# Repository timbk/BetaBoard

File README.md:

# BetaBoard

A particle detector built for cost-effectiveness when ordered at O(100) pieces.

The detector concept is adapted from the [DIY Particle Detector Project](https://github.com/ozel/DIY_particle_detector) by Oliver Keller.

## Hardware Revisions

| Revision 1 | Revision 2 |
| :---: | :---: |
|  |  |
| [Schematic](hardware/betaBoard_r1.0/pdf/betaBoard_sch.pdf) [Layout](hardware/betaBoard_r1.0/pdf/betaBoard_pdf.pdf) | [Schematic](hardware/betaBoard_r2.0/betaBoard_r2.0_sch.pdf) [Layout](hardware/betaBoard_r2.0/betaBoard_r2.0_pcb.pdf) [Component Positions](hardware/betaBoard_r2.0/betaBoard_r2.0_positions.pdf) |
| Initial protoype: Working with adjustemtns to a few component values. Requires a lot of electrical and conductive tape to assemble. Designed for 16 diodes with the option to measure coincidences. | Streamlined redesign. Mainly adding a PCB casing to block light and radio imission. Attempting to add a simple alpha particle detector channel by stripping the isolation off of a diode (not successfull yet). Single channel with 6 diodes in parallel. Using additional ADC channels with less gain for debugging and potential experiments with scintillators. |

## Experiment Ideas

* Time distribution of pulses
* Rate vs distance (1/d^2 + offset)
* Absorption coefficient
    * Increase material thickness between detector and source
* Spectroscopy?? (alphas, sand down diode?
* Balloon in cellar

## Serial interface

* `T` `T <block_index> <timestamp_us> <overflow> # <sample_0> <sample_1> .. <sample_N>`
    * `block_index`: uint16_t, mainly relevant for debugging
    * `timestamp_us`: uint64_t, Trigger point timestamp in micro seconds since start of the measurement
    * `overflow`: bool, set to 1 if an overflow happend prior to this sample
    * `sample_n`:  int16_t, samples from the triggered waveform

## PCB

[Schematic](betaBoard/pdf/betaBoard_sch.pdf)
[Layout](betaBoard/pdf/betaBoard_pdf.pdf)

The goal was to keep it small to keep the PCB cost low and to make it fit easily.
Components were chosen to keep the price low and based on availablility at the chosen manufacturer.

## Ideas

* Strip detector with 4 pixels?
* File down SMD LEDs for less absorption?
* 3D-Printed Case?
* Interconnect multiple detectors?

## R2.0 ideas

* Put VCC on interconnect instead of 3V3
* Review diode cutout size
* Increase power supply castellated hole distance
* Increase LDO heat sink plane size
* Think about how usefull the coincidence concept is: 2x2 = 2+2 = 4!
* Silk to highlight Diode grouping
* Seperate bulk capacitor on 5V rail for analog

## Noise calculations

* Spice simulation: peak of ca. 40 $\mu\text{V}/\sqrt{\text{Hz}}$
    * Resistor thermal noise: $\sqrt{4k_BTR}\approx 400 ~ \text{nV/}\sqrt{\text{Hz}}$
    * LM358 input noise is ca. 40 $\text{nV}/\sqrt{\text{Hz}}$
    * Gain of second stage is ca. 100 for the peak frequency
    * => Resistor thermal noise is dominant part in simulation, LM385 noise should be negligible
        * $100 \cdot 400~\text{nV}/\sqrt{\text{Hz}} \approx 40~\mu\text{V}/\sqrt{\text{Hz}}$

## Potential signal sources

* 10g KCl has ca. 164 Bq.
* Estimate of geometric acceptency at 2 cm distance: $A = \frac{4 \cdot 7.5~\text{mm}^2} {4\pi\cdot (20~\text{mm})^2} \approx 0.006$
    * With perfect efficiency: ca. 1 Hz

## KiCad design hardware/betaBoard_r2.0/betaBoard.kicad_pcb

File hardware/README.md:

# Hardware Files

## betaBoard.pretty

Custom KiCad footprints.

## betaBoard_r1.0

First revision of the PCB.

Design concepts:
* 4 Channels
    * adding channles came without significant cost (only opamps and passives)
    * 2 Channel on the back are expensive to populate
* Header to connect PD with leads
* External power header for up to 12 V to increase diode bias
* RP2040 allows simple programming via USB
    * Can be done by the user without special tools
* Allow options for different diode placement
    * More diodes yield more sensitivity

Good:
* MCU, buttons, USB etc work perfectly out of the box :D

Challenges:
* High USB noise (1kHz spikes)
    * R14 requires a parallel C to get rid of noise from USB line
        * 1uF seems to help but does not seem sufficient (Could try 10uF, have 0603)
        * could increase R by factor 10
    * Try larger bulk capacitance (100uF or 1000uF)
        * 1000 uF seems to help!
        * Might be change in current draw
        * Cable length (resistance) seems to have an effect
    * Useing seperate diodes for the two supplies could help (diode voltage drop might depend on current)
    * TODO: Try if battery operation is better (helps to exclude potential points where 1 kHz noise couples)
* Is 40 MOhm working with the input impedance of LM358??
* Cut up groundplane at the PDs is probably not optimal
* Keep loop areas even smaller (I don't think it's the source of issues, but would feel better)
* USB port shielding is connected to GND. This might not be the optimal solution
    * Next: Add 2 0603 footprints? (allows open, short, 1MOhm+C)

## betaBoard_r1.1

Next revision. Work in progress.

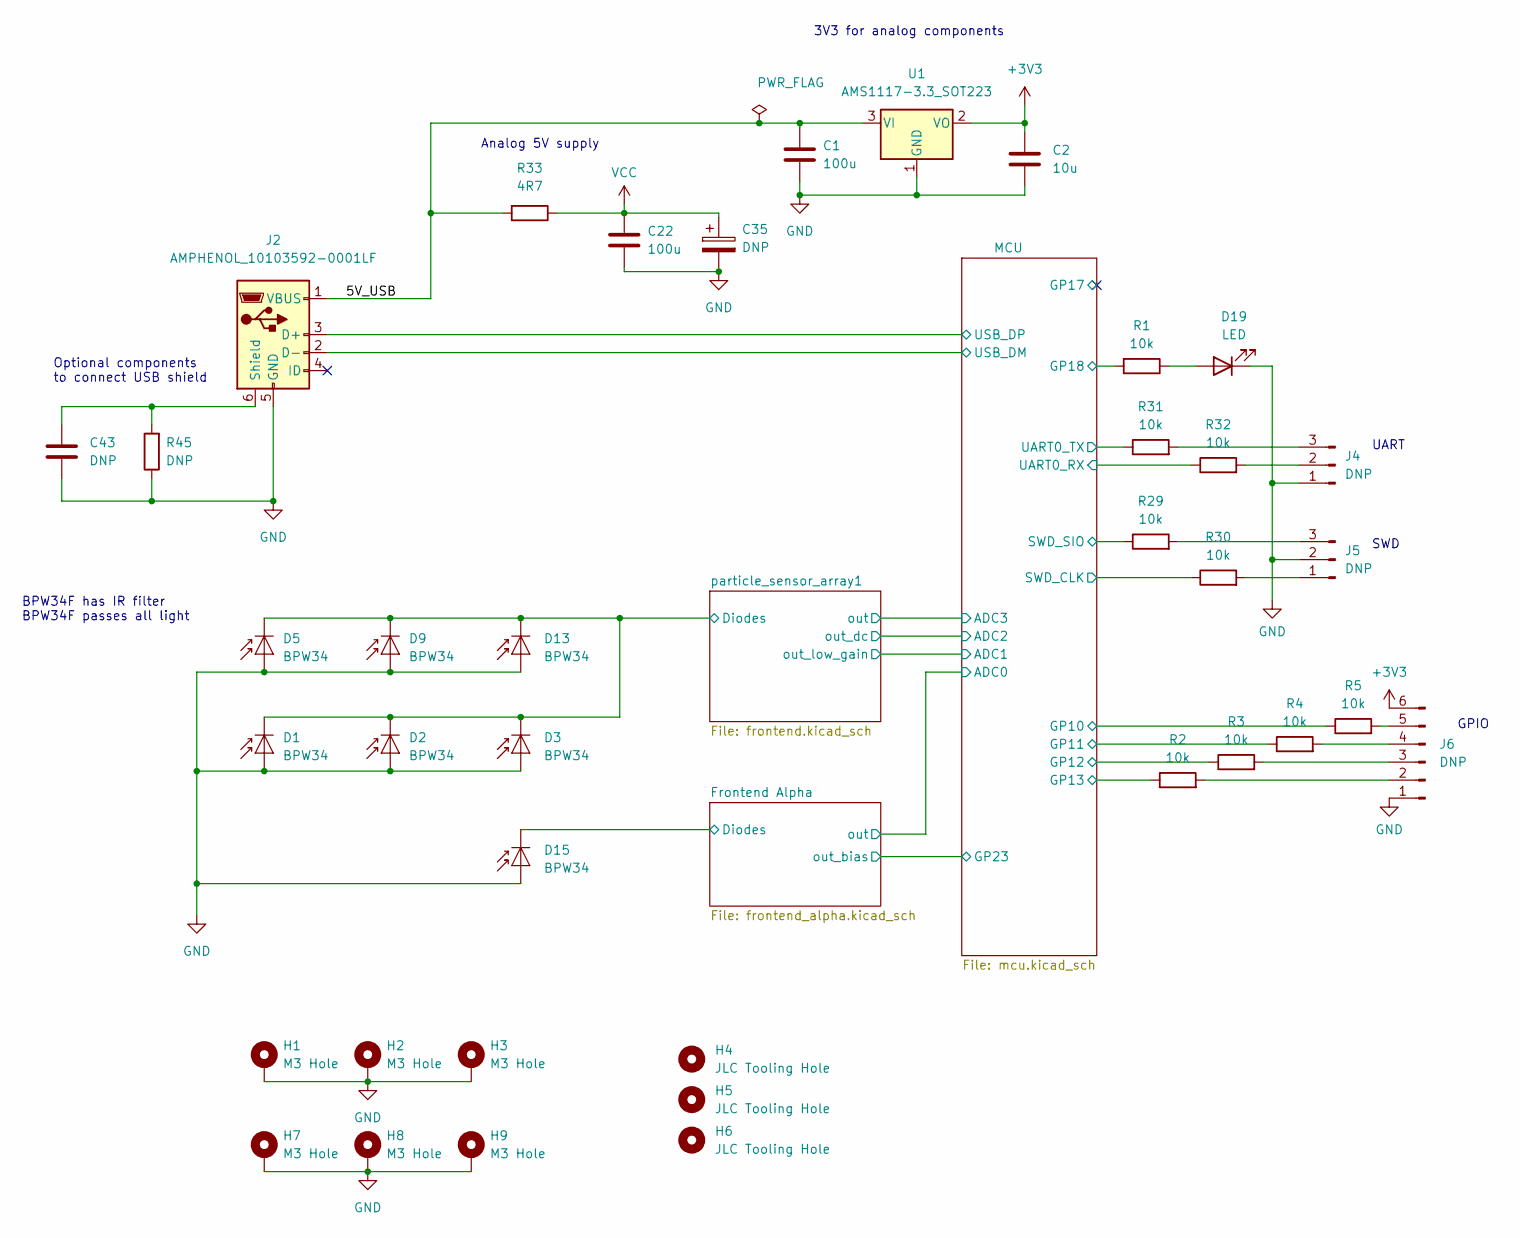
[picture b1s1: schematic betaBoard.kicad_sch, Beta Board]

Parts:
C1, C22: 100u; C_1206_3216Metric
C2: 10u; C_1206_3216Metric
C35: DNP; CP_Radial_D10.0mm_P5.00mm
C43: DNP; C_0603_1608Metric
D1, D2, D3, D5, D9, D13, D15: BPW34; Osram_BPW34S-SMD
D19: LED; LED_0603_1608Metric
H1, H2, H3, H7, H8, H9: M3 Hole; MountingHole_2.7mm_M2.5_DIN965_Pad
H4, H5, H6: JLC Tooling Hole; JLC_tooling_hole
J2: AMPHENOL_10103592-0001LF
J4, J5: DNP; PinHeader_1x03_P2.54mm_Vertical
J6: DNP; PinHeader_1x06_P2.54mm_Vertical
R1, R2, R3, R4, R5, R29, R30, R31, R32: 10k; R_0603_1608Metric
R33: 4R7; R_0603_1608Metric
R45: DNP; R_0603_1608Metric
U1: AMS1117-3.3_SOT223; SOT-223-3_TabPin2

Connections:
+3V3: C2.1, J6.6, U1.2 (VO); also elsewhere on the board
/5V_USB: C1.1, J2.1 (VBUS), R33.2, U1.3 (VI)
/Frontend Alpha/Diodes: D15.1 (K); also elsewhere on the board
/MCU/GP10: R5.1; also elsewhere on the board
/MCU/GP11: R4.1; also elsewhere on the board
/MCU/GP12: R3.1; also elsewhere on the board
/MCU/GP13: R2.1; also elsewhere on the board
/MCU/GP18: R1.2; also elsewhere on the board
/MCU/SWD_CLK: R30.1; also elsewhere on the board
/MCU/SWD_SIO: R29.1; also elsewhere on the board
/MCU/UART0_RX: R32.1; also elsewhere on the board
/MCU/UART0_TX: R31.1; also elsewhere on the board
/MCU/USB_DM: J2.2 (D-); also elsewhere on the board
/MCU/USB_DP: J2.3 (D+); also elsewhere on the board
/particle_sensor_array1/Diodes: D1.1 (K), D2.1 (K), D3.1 (K), D5.1 (K), D9.1 (K), D13.1 (K); also elsewhere on the board
GND: C1.2, C2.2, C22.2, C35.2, C43.2, D1.2 (A), D2.2 (A), D3.2 (A), D5.2 (A), D9.2 (A), D13.2 (A), D15.2 (A), D19.1 (K), H1.1, H2.1, H3.1, H7.1, H8.1, H9.1, J2.5 (GND), J4.1, J5.2, J6.1, R45.1, U1.1 (GND); also elsewhere on the board
unnamed: D19.2 (A), R1.1
unnamed: C43.1, J2.6 (Shield), R45.2
unnamed: J4.2, R32.2
unnamed: J4.3, R31.2
unnamed: J5.1, R30.2
unnamed: J5.3, R29.2
unnamed: J6.2, R2.2
unnamed: J6.3, R3.2
unnamed: J6.4, R4.2
unnamed: J6.5, R5.2
VCC: C22.1, C35.1, R33.1; also elsewhere on the board

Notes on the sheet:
SWD
GPIO
Analog 5V supply
3V3 for analog components
BPW34F has IR filter BPW34F passes all light
UART
Optional components to connect USB shield

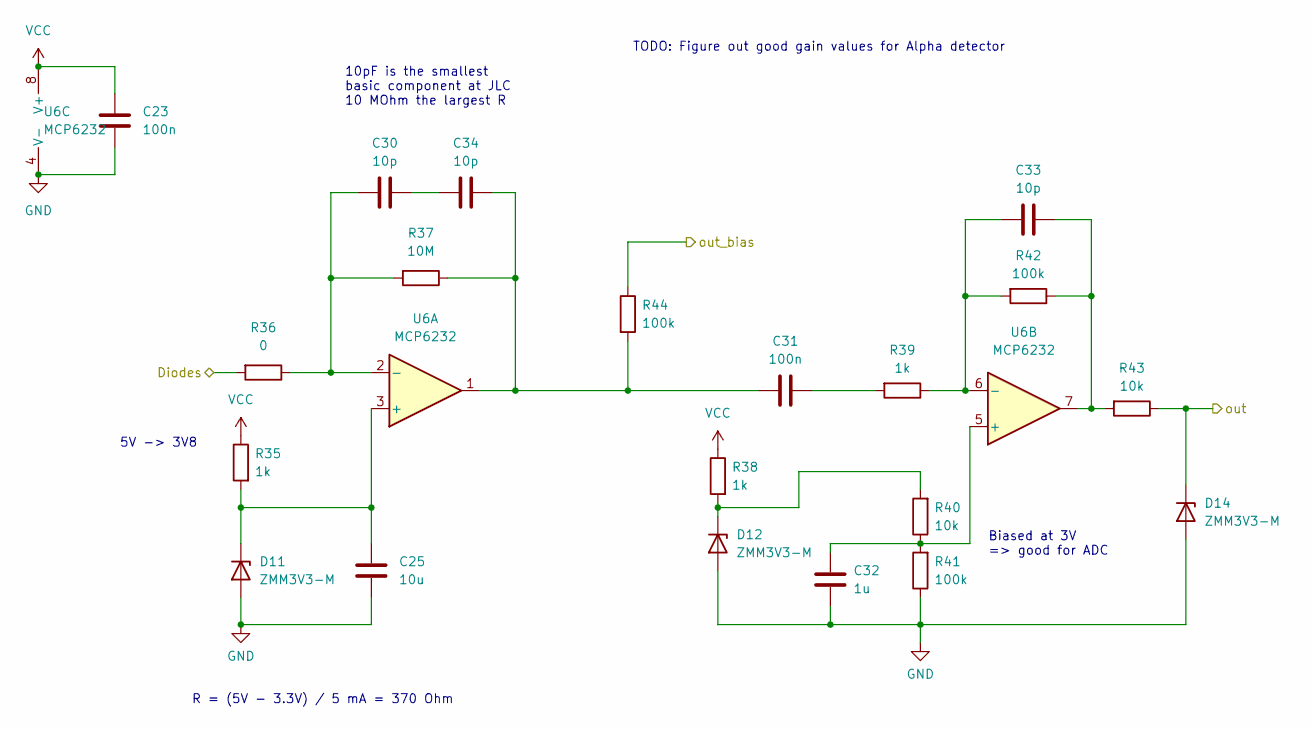
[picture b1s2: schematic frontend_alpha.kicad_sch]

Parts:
C23, C31: 100n; C_0603_1608Metric
C25: 10u; C_0603_1608Metric
C30, C33, C34: 10p; C_0603_1608Metric
C32: 1u; C_0603_1608Metric
D11, D12, D14: ZMM3V3-M; D_MiniMELF
R35, R38, R39: 1k; R_0603_1608Metric
R36: 0; R_0603_1608Metric
R37: 10M; R_0603_1608Metric
R40, R43: 10k; R_0603_1608Metric
R41, R42, R44: 100k; R_0603_1608Metric
U6: MCP6232; SOIC-8_3.9x4.9mm_P1.27mm

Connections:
/Frontend Alpha/Diodes: R36.2; also elsewhere on the board
/Frontend Alpha/out: D14.1 (K), R43.1; also elsewhere on the board
/Frontend Alpha/out_bias: R44.1; also elsewhere on the board
GND: C23.2, C25.2, C32.2, D11.2 (A), D12.2 (A), D14.2 (A), R41.1, U6.4 (V-); also elsewhere on the board
unnamed: C30.2, C34.1
unnamed: C31.1, C34.2, R37.1, R44.2, U6.1
unnamed: C31.2, R39.2
unnamed: C33.2, R42.1, R43.2, U6.7
unnamed: C25.1, D11.1 (K), R35.2, U6.3 (+)
unnamed: D12.1 (K), R38.2, R40.2
unnamed: C30.1, R36.1, R37.2, U6.2 (-)
unnamed: C32.1, R40.1, R41.2, U6.5 (+)
unnamed: C33.1, R39.1, R42.2, U6.6 (-)
VCC: C23.1, R35.1, R38.1, U6.8 (V+); also elsewhere on the board

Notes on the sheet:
5V -> 3V8
TODO: Figure out good gain values for Alpha detector
10pF is the smallest basic component at JLC 10 MOhm the largest R
R = (5V - 3.3V) / 5 mA = 370 Ohm
Biased at 3V => good for ADC

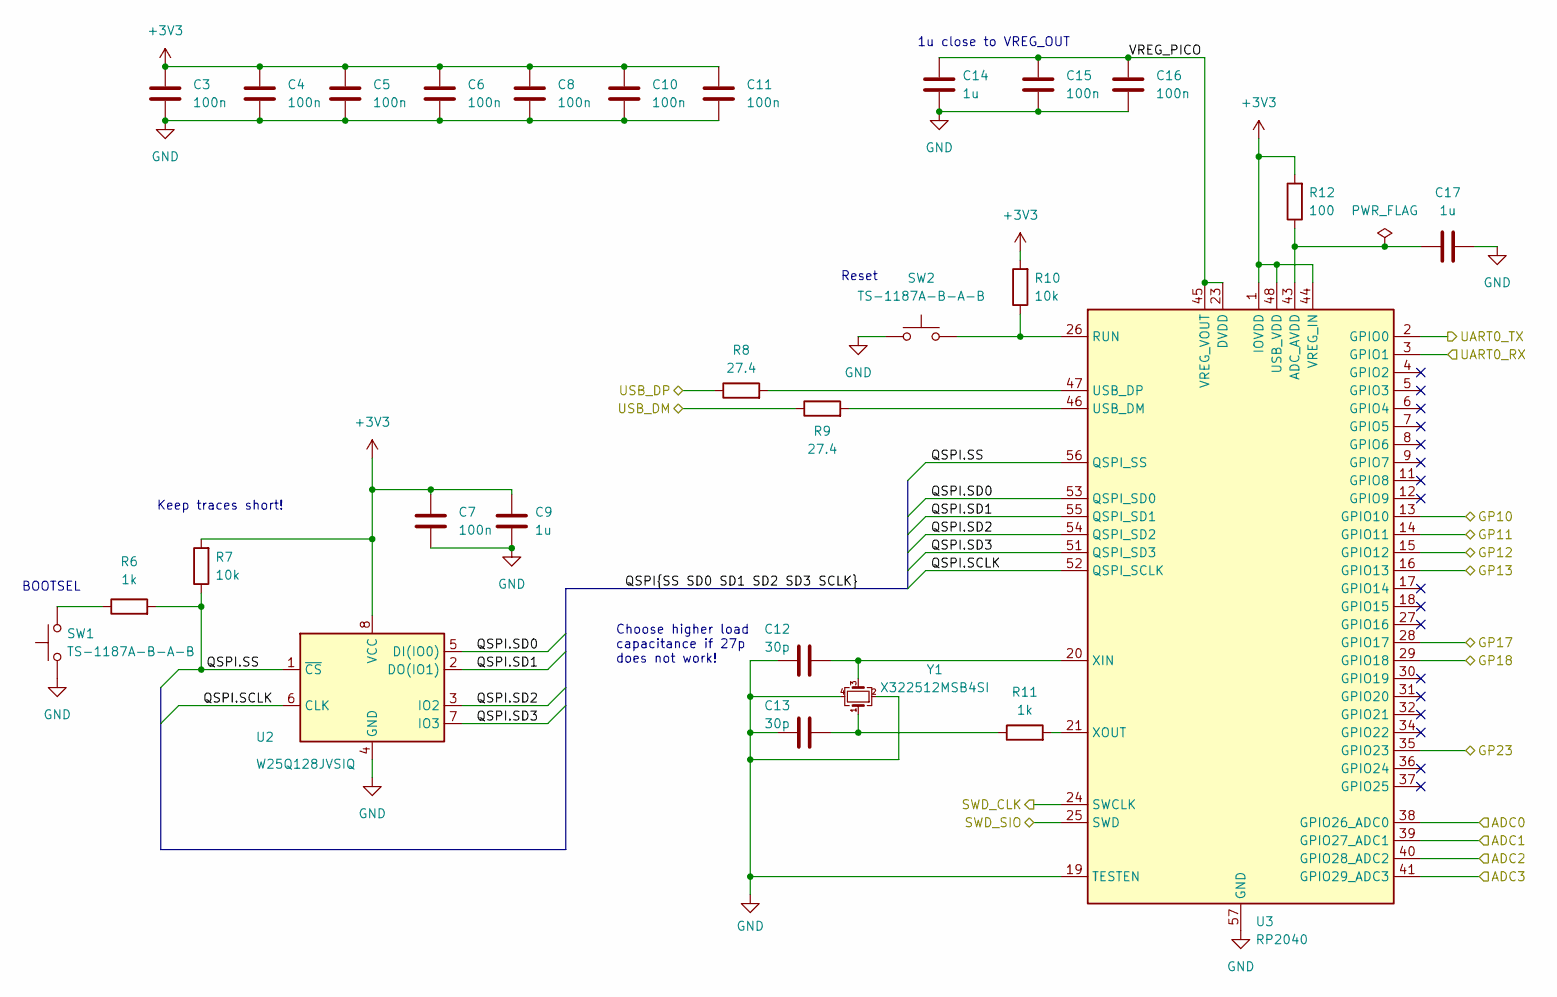
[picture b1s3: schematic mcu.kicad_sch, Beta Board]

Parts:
C3, C4, C5, C6, C7, C8, C10, C11, C15, C16: 100n; C_0603_1608Metric
C9, C14, C17: 1u; C_0603_1608Metric
C12, C13: 30p; C_0603_1608Metric
R6, R11: 1k; R_0603_1608Metric
R7, R10: 10k; R_0603_1608Metric
R8, R9: 27.4; R_0603_1608Metric
R12: 100; R_0603_1608Metric
SW1, SW2: TS-1187A-B-A-B
U2: W25Q128JVSIQ; SOIC-8_5.23x5.23mm_P1.27mm
U3: RP2040; QFN-56-1EP_7x7mm_P0.4mm_EP3.2x3.2mm
Y1: X322512MSB4SI; Crystal_SMD_3225-4Pin_3.2x2.5mm

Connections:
+3V3: C3.1, C4.1, C5.1, C6.1, C7.1, C8.1, C9.1, C10.1, C11.1, R7.2, R10.2, R12.2, U2.8 (VCC), U3.1 (IOVDD), U3.10 (IOVDD), U3.22 (IOVDD), U3.33 (IOVDD), U3.42 (IOVDD), U3.44 (VREG_IN), U3.48 (USB_VDD), U3.49 (IOVDD); also elsewhere on the board
/Frontend Alpha/out: U3.38 (GPIO26_ADC0); also elsewhere on the board
/Frontend Alpha/out_bias: U3.35 (GPIO23); also elsewhere on the board
/MCU/ADC1: U3.39 (GPIO27_ADC1); also elsewhere on the board
/MCU/ADC2: U3.40 (GPIO28_ADC2); also elsewhere on the board
/MCU/ADC3: U3.41 (GPIO29_ADC3); also elsewhere on the board
/MCU/GP10: U3.13 (GPIO10); also elsewhere on the board
/MCU/GP11: U3.14 (GPIO11); also elsewhere on the board
/MCU/GP12: U3.15 (GPIO12); also elsewhere on the board
/MCU/GP13: U3.16 (GPIO13); also elsewhere on the board
/MCU/GP17: U3.28 (GPIO17)
/MCU/GP18: U3.29 (GPIO18); also elsewhere on the board
/MCU/QSPI.SCLK: U2.6 (CLK), U3.52 (QSPI_SCLK)
/MCU/QSPI.SD0: U2.5 (DI(IO0)), U3.53 (QSPI_SD0)
/MCU/QSPI.SD1: U2.2 (DO(IO1)), U3.55 (QSPI_SD1)
/MCU/QSPI.SD2: U2.3 (IO2), U3.54 (QSPI_SD2)
/MCU/QSPI.SD3: U2.7 (IO3), U3.51 (QSPI_SD3)
/MCU/QSPI.SS: R6.2, R7.1, U2.1 (~CS), U3.56 (QSPI_SS)
/MCU/SWD_CLK: U3.24 (SWCLK); also elsewhere on the board
/MCU/SWD_SIO: U3.25 (SWD); also elsewhere on the board
/MCU/UART0_RX: U3.3 (GPIO1); also elsewhere on the board
/MCU/UART0_TX: U3.2 (GPIO0); also elsewhere on the board
/MCU/USB_DM: R9.1; also elsewhere on the board
/MCU/USB_DP: R8.1; also elsewhere on the board
/MCU/VREG_PICO: C14.1, C15.1, C16.1, U3.23 (DVDD), U3.45 (VREG_VOUT), U3.50 (DVDD)
GND: C3.2, C4.2, C5.2, C6.2, C7.2, C8.2, C9.2, C10.2, C11.2, C12.1, C13.2, C14.2, C15.2, C16.2, C17.2, SW1.1, SW2.1, U2.4 (GND), U3.19 (TESTEN), U3.57 (GND), Y1.2, Y1.4; also elsewhere on the board
unnamed: C13.1, R11.1, Y1.1
unnamed: R6.1, SW1.2
unnamed: C17.1, R12.1, U3.43 (ADC_AVDD)
unnamed: R10.1, SW2.2, U3.26 (RUN)
unnamed: R9.2, U3.46 (USB_DM)
unnamed: R8.2, U3.47 (USB_DP)
unnamed: C12.2, U3.20 (XIN), Y1.3
unnamed: R11.2, U3.21 (XOUT)

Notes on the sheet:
Choose higher load capacitance if 27p does not work!
Reset
Keep traces short!
1u close to VREG_OUT
BOOTSEL

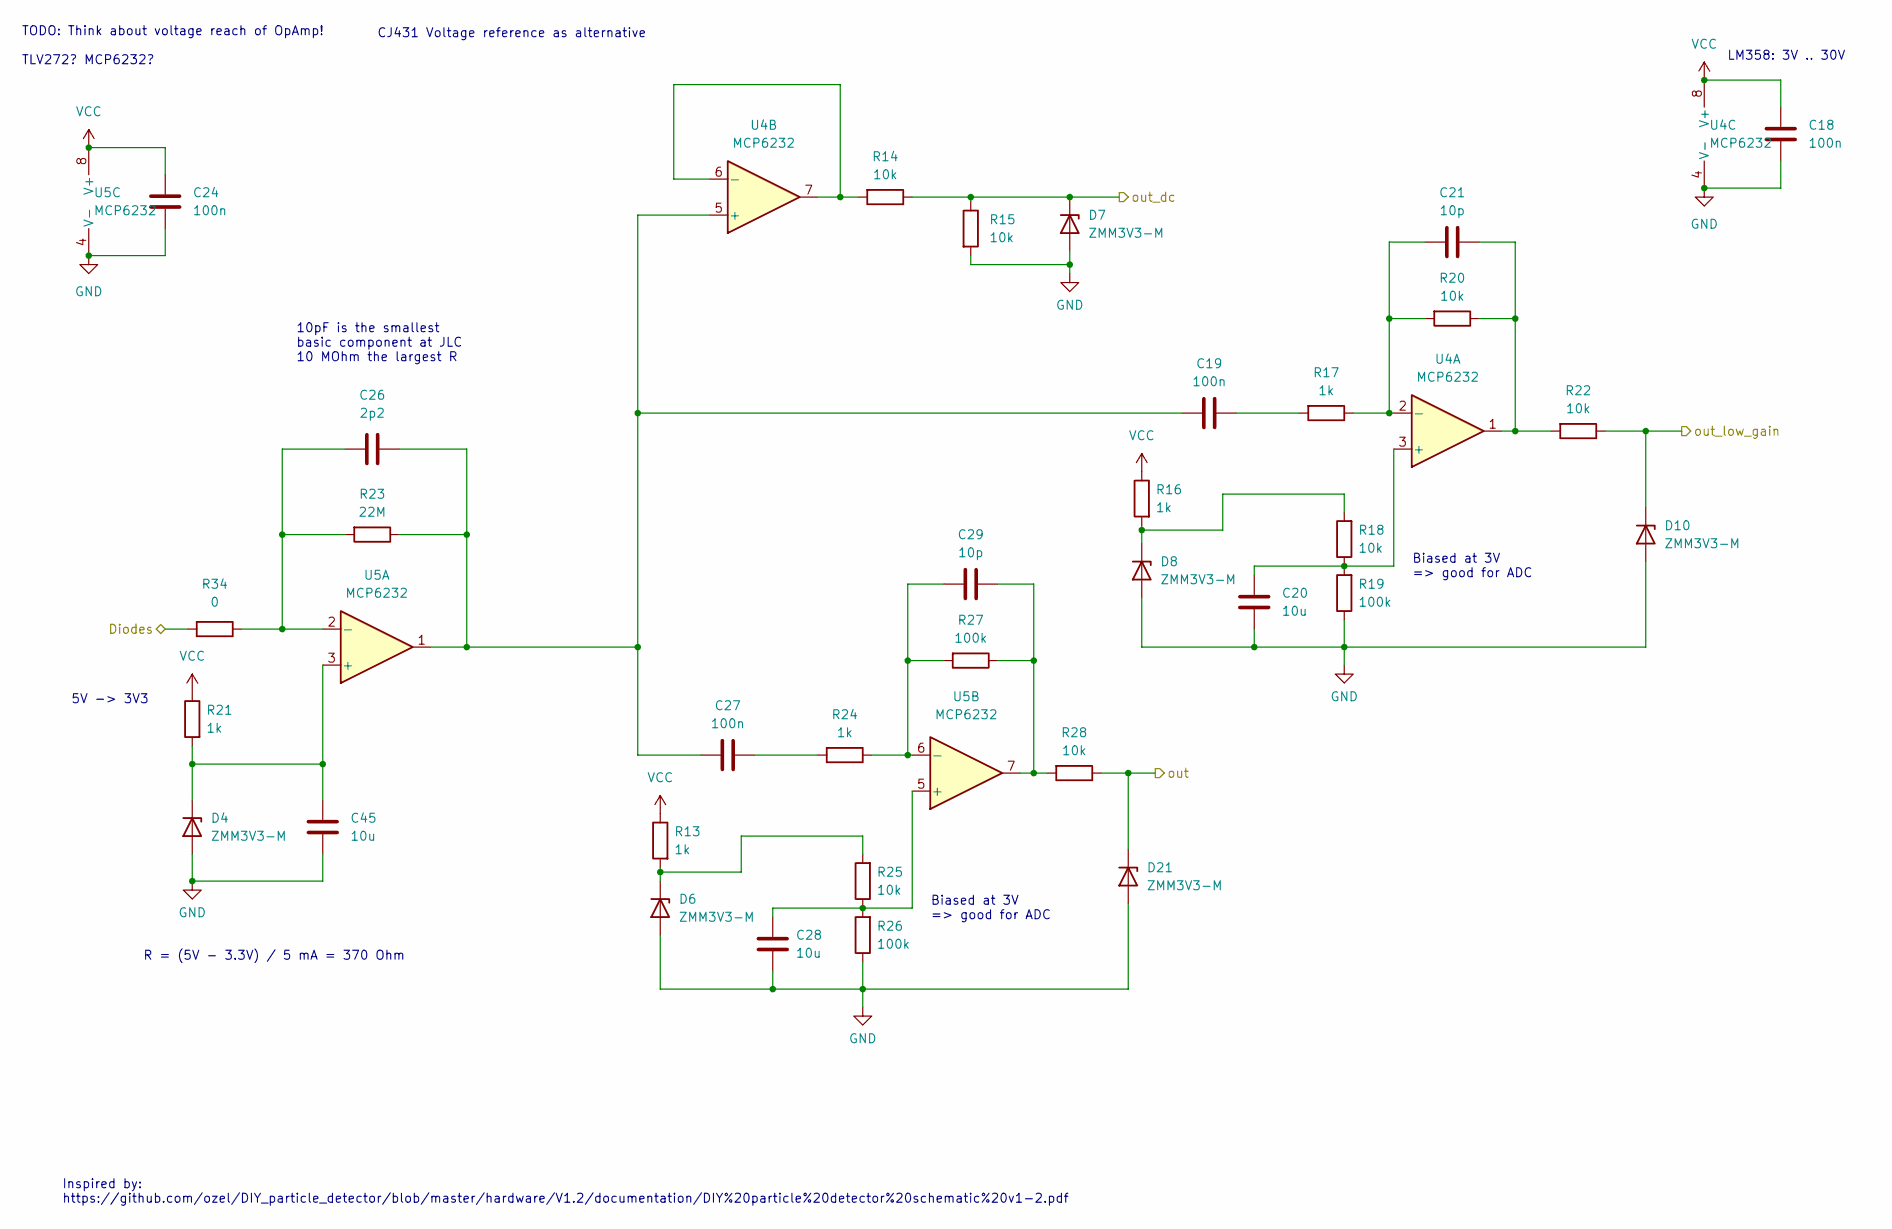
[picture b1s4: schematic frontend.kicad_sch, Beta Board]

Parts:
C18, C19, C24, C27: 100n; C_0603_1608Metric
C20, C28, C45: 10u; C_0603_1608Metric
C21, C29: 10p; C_0603_1608Metric
C26: 2p2; C_0603_1608Metric
D4, D6, D7, D8, D10, D21: ZMM3V3-M; D_MiniMELF
R13, R16, R17, R21, R24: 1k; R_0603_1608Metric
R14, R15, R18, R20, R22, R25, R28: 10k; R_0603_1608Metric
R19, R26, R27: 100k; R_0603_1608Metric
R23: 22M; R_0603_1608Metric
R34: 0; R_0603_1608Metric
U4, U5: MCP6232; SOIC-8_3.9x4.9mm_P1.27mm

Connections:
/MCU/ADC1: D10.1 (K), R22.1; also elsewhere on the board
/MCU/ADC2: D7.1 (K), R14.1, R15.1; also elsewhere on the board
/MCU/ADC3: D21.1 (K), R28.1; also elsewhere on the board
/particle_sensor_array1/Diodes: R34.2; also elsewhere on the board
GND: C18.2, C20.2, C24.2, C28.2, C45.2, D4.2 (A), D6.2 (A), D7.2 (A), D8.2 (A), D10.2 (A), D21.2 (A), R15.2, R19.1, R26.1, U4.4 (V-), U5.4 (V-); also elsewhere on the board
unnamed: C19.2, R17.2
unnamed: C21.2, R20.1, R22.2, U4.1
unnamed: C27.2, R24.2
unnamed: C29.2, R27.1, R28.2, U5.7
unnamed: C45.1, D4.1 (K), R21.2, U5.3 (+)
unnamed: D6.1 (K), R13.2, R25.2
unnamed: D8.1 (K), R16.2, R18.2
unnamed: C20.1, R18.1, R19.2, U4.3 (+)
unnamed: C21.1, R17.1, R20.2, U4.2 (-)
unnamed: C19.1, C26.2, C27.1, R23.1, U4.5 (+), U5.1
unnamed: R14.2, U4.6 (-), U4.7
unnamed: C26.1, R23.2, R34.1, U5.2 (-)
unnamed: C28.1, R25.1, R26.2, U5.5 (+)
unnamed: C29.1, R24.1, R27.2, U5.6 (-)
VCC: C18.1, C24.1, R13.1, R16.1, R21.1, U4.8 (V+), U5.8 (V+); also elsewhere on the board

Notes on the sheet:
Inspired by: https://github.com/ozel/DIY_particle_detector/blob/master/hardware/V1.2/documentation/DIY%20particle%20detector%20schematic%20v1-2.pdf
TODO: Think about voltage reach of OpAmp! TLV272? MCP6232?
5V -> 3V3
CJ431 Voltage reference as alternative
10pF is the smallest basic component at JLC 10 MOhm the largest R
Biased at 3V => good for ADC
R = (5V - 3.3V) / 5 mA = 370 Ohm
LM358: 3V .. 30V

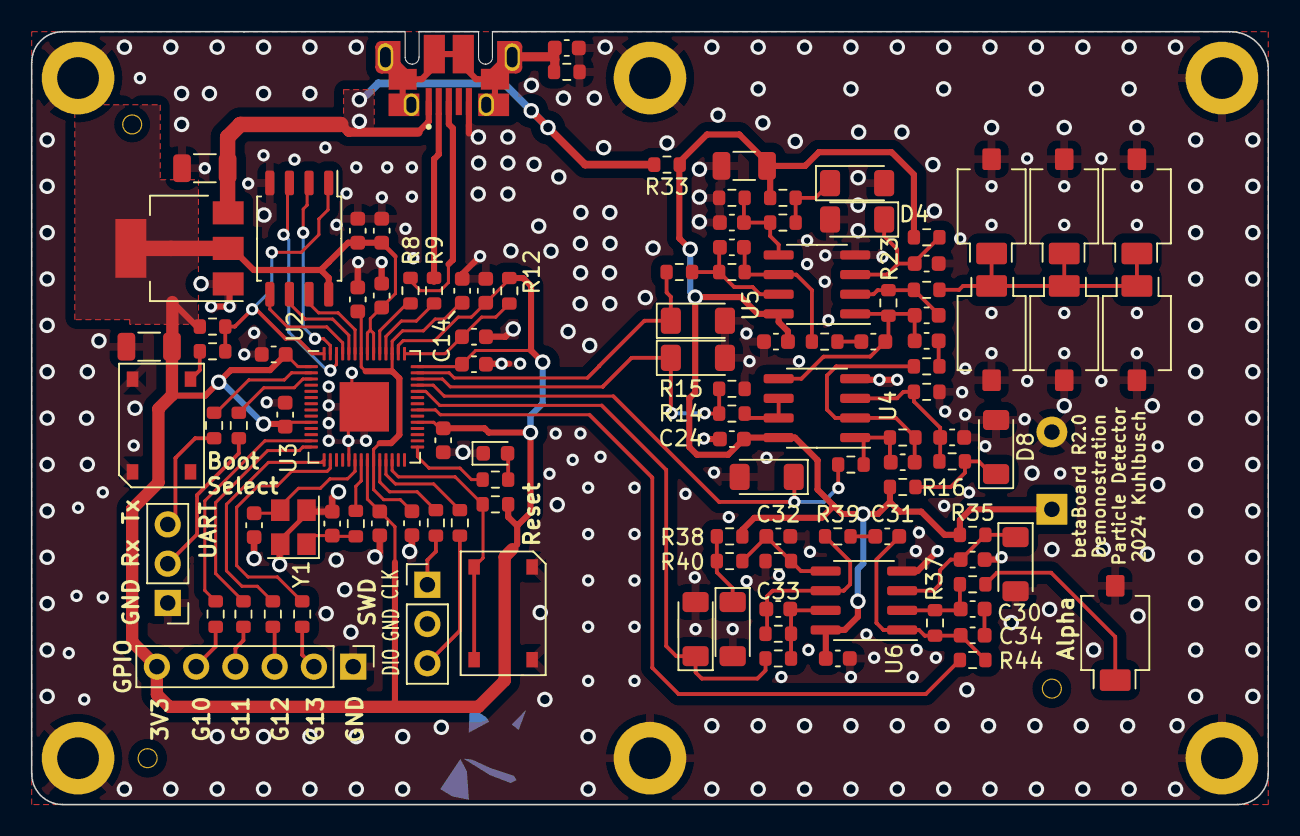
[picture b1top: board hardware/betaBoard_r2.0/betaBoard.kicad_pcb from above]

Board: 2 copper layers, 80.0 x 50.0 mm, 121 parts (1 on the bottom side), 70 nets.

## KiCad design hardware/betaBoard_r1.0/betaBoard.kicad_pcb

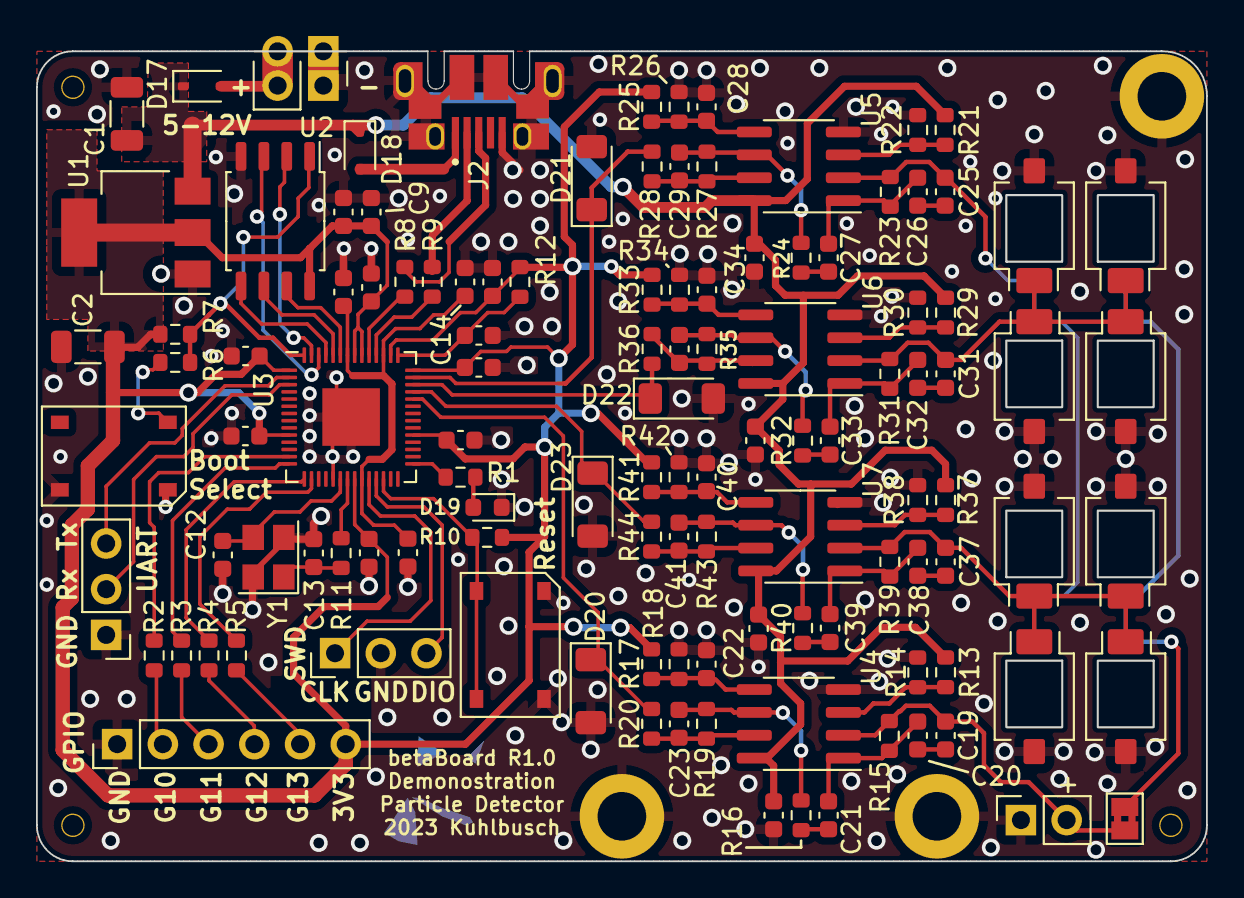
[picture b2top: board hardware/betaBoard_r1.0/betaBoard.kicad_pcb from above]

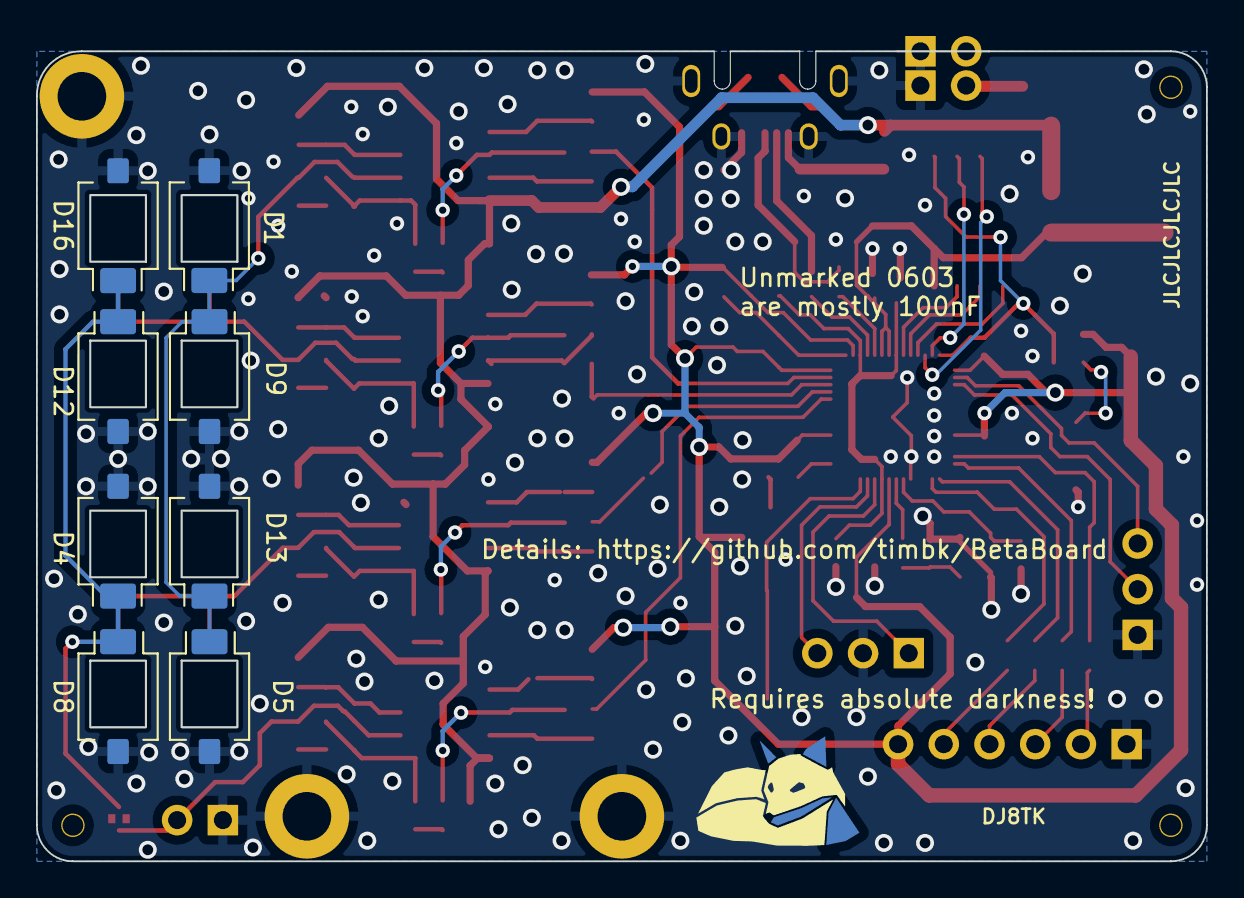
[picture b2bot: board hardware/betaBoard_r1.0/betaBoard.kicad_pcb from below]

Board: 2 copper layers, 65.0 x 45.0 mm, 131 parts (8 on the bottom side), 73 nets.

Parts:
C1, C2: 10u; C_1206_3216Metric
C3, C4, C5, C6, C7, C8, C10, C11, C15, C16, C18, C22, C24, C28, C30, C34, C36, C40: 100n; C_0603_1608Metric
C9, C14, C17: 1u; C_0603_1608Metric
C12, C13: 30p; C_0603_1608Metric
C19, C20, C25, C26, C31, C32, C37, C38: 10p; C_0603_1608Metric
C21, C27, C33, C39: 470n; C_0603_1608Metric
C23, C29, C35, C41: 47p; C_0603_1608Metric
D1, D4, D5, D8, D9, D12, D13, D16: DNP; Osram_BPW34S-SMD
D2, D3, D6, D7, D10, D11, D14, D15: BPW34-SMD; Osram_BPW34S-SMD_hole
D17, D18: 1N5819WS; D_SOD-323
D19: LED; LED_0603_1608Metric
D20, D21, D22, D23: ZMM3V3-M; D_MiniMELF
H1, H2, H3: M3 Hole; MountingHole_2.7mm_M2.5_DIN965_Pad
H4, H5, H6: JLC Tooling Hole; JLC_tooling_hole
J1: DNP; PinHeader_1x02_P2.54mm_castellation
J2: AMPHENOL_10103592-0001LF
J3: DNP; PinSocket_1x02_P2.54mm_Vertical
J4, J5: DNP; PinHeader_1x03_P2.54mm_Vertical
J6: DNP; PinHeader_1x06_P2.54mm_Vertical
JP1: DNP; SolderJumper-2_P1.3mm_Bridged2Bar_Pad1.0x1.5mm
R1, R7, R10, R17, R18, R20, R25, R26, R28, R33, R34, R36, R41, R42, R44: 10k; R_0603_1608Metric
R2, R3, R4, R5, R6, R11: 1k; R_0603_1608Metric
R8, R9: 27.4; R_0603_1608Metric
R12: 100; R_0603_1608Metric
R13, R21, R29, R37: 4k7; R_0603_1608Metric
R14, R22, R30, R38: 15k; R_0603_1608Metric
R15, R23, R31, R39: 47M; R_0603_1608Metric
R16, R24, R32, R40: 4K7; R_0603_1608Metric
R19, R27, R35, R43: 1M; R_0603_1608Metric
SW1, SW2: C26638; TS-1187A-B-A-B
U1: AMS1117-3.3_SOT223; SOT-223-3_TabPin2
U2: W25Q128JVSIQ; SOIC-8_5.23x5.23mm_P1.27mm
U3: RP2040; QFN-56-1EP_7x7mm_P0.4mm_EP3.2x3.2mm
U4, U5, U6, U7: LM358; SOIC-8_3.9x4.9mm_P1.27mm
Y1: X322512MSB4SI; Crystal_SMD_3225-4Pin_3.2x2.5mm

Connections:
+3V3: C2.1, C3.1, C4.1, C5.1, C6.1, C7.1, C8.1, C9.1, C10.1, C11.1, J6.6, R7.2, R10.2, R12.2, R17.2, R25.2, R33.2, R41.2, U1.2 (VO), U2.8 (VCC), U3.1 (IOVDD), U3.10 (IOVDD), U3.22 (IOVDD), U3.33 (IOVDD), U3.42 (IOVDD), U3.44 (VREG_IN), U3.48 (USB_VDD), U3.49 (IOVDD)
/5V_USB: D18.2 (A), J2.1 (VBUS)
/MCU/ADC0: D20.1 (K), R20.1, U3.38 (GPIO26_ADC0)
/MCU/ADC1: D23.1 (K), R44.1, U3.39 (GPIO27_ADC1)
/MCU/ADC2: D22.1 (K), R36.1, U3.40 (GPIO28_ADC2)
/MCU/ADC3: D21.1 (K), R28.1, U3.41 (GPIO29_ADC3)
/MCU/GP10: R2.1, U3.13 (GPIO10)
/MCU/GP11: R3.1, U3.14 (GPIO11)
/MCU/GP12: R4.1, U3.15 (GPIO12)
/MCU/GP13: R5.1, U3.16 (GPIO13)
/MCU/GP18: R1.2, U3.29 (GPIO18)
/MCU/QSPI.SCLK: U2.6 (CLK), U3.52 (QSPI_SCLK)
/MCU/QSPI.SD0: U2.5 (DI(IO0)), U3.53 (QSPI_SD0)
/MCU/QSPI.SD1: U2.2 (DO(IO1)), U3.55 (QSPI_SD1)
/MCU/QSPI.SD2: U2.3 (IO2), U3.54 (QSPI_SD2)
/MCU/QSPI.SD3: U2.7 (IO3), U3.51 (QSPI_SD3)
/MCU/QSPI.SS: R6.2, R7.1, U2.1 (~CS), U3.56 (QSPI_SS)
/MCU/SWD_CLK: J5.1, U3.24 (SWCLK)
/MCU/SWD_SIO: J5.3, U3.25 (SWD)
/MCU/UART0_RX: J4.2, U3.3 (GPIO1)
/MCU/UART0_TX: J4.3, U3.2 (GPIO0)
/MCU/USB_DM: J2.2 (D-), R9.1
/MCU/USB_DP: J2.3 (D+), R8.1
/MCU/VREG_PICO: C14.1, C15.1, C16.1, U3.23 (DVDD), U3.45 (VREG_VOUT), U3.50 (DVDD)
/particle_sensor_array1/Diodes: C25.1, D1.1 (K), D5.1 (K), D9.1 (K), D13.1 (K), R23.2, U5.2 (-)
/particle_sensor_array2/Diodes: C31.1, D2.1 (K), D6.1 (K), D10.1 (K), D14.1 (K), R31.2, U6.2 (-)
/particle_sensor_array3/Diodes: C37.1, D3.1 (K), D7.1 (K), D11.1 (K), D15.1 (K), R39.2, U7.2 (-)
/particle_sensor_array/Diodes: C19.1, J3.2, JP1.2 (B), R15.2, U4.2 (-)
GND: C1.2, C2.2, C3.2, C4.2, C5.2, C6.2, C7.2, C8.2, C9.2, C10.2, C11.2, C12.1, C13.2, C14.2, C15.2, C16.2, C17.2, C18.2, C22.2, C24.2, C28.2, C30.2, C34.2, C36.2, C40.2, D1.2 (A), D2.2 (A), D3.2 (A), D4.2 (A), D5.2 (A), D6.2 (A), D7.2 (A), D8.2 (A), D9.2 (A), D10.2 (A), D11.2 (A), D12.2 (A), D13.2 (A), D14.2 (A), D15.2 (A), D16.2 (A), D19.1 (K), D20.2 (A), D21.2 (A), D22.2 (A), D23.2 (A), H1.1, H2.1, H3.1, J1.1, J2.5 (GND), J2.6 (Shield), J3.1, J4.1, J5.2, J6.1, R14.2, R18.1, R22.2, R26.1, R30.2, R34.1, R38.2, R42.1, SW1.1, SW2.1, U1.1 (GND), U2.4 (GND), U3.19 (TESTEN), U3.57 (GND), U4.4 (V-), U5.4 (V-), U6.4 (V-), U7.4 (V-), Y1.2, Y1.4
unnamed: C13.1, R11.1, Y1.1
unnamed: C19.2, C20.1
unnamed: C20.2, C21.1, R15.1, U4.1
unnamed: C21.2, R16.2
unnamed: C23.2, R19.1, R20.2, U4.7
unnamed: C25.2, C26.1
unnamed: C26.2, C27.1, R23.1, U5.1
unnamed: C27.2, R24.2
unnamed: C29.2, R27.1, R28.2, U5.7
unnamed: C31.2, C32.1
unnamed: C32.2, C33.1, R31.1, U6.1
unnamed: C33.2, R32.2
unnamed: C35.2, R35.1, R36.2, U6.7
unnamed: C37.2, C38.1
unnamed: C38.2, C39.1, R39.1, U7.1
unnamed: C39.2, R40.2
unnamed: C41.2, R43.1, R44.2, U7.7
unnamed: D4.1 (K), D8.1 (K), D12.1 (K), D16.1 (K), JP1.1 (A)
unnamed: D17.2 (A), J1.2
unnamed: D19.2 (A), R1.1
unnamed: J6.2, R2.2
unnamed: J6.3, R3.2
unnamed: J6.4, R4.2
unnamed: J6.5, R5.2
unnamed: R6.1, SW1.2
unnamed: C17.1, R12.1, U3.43 (ADC_AVDD)
unnamed: R10.1, SW2.2, U3.26 (RUN)
unnamed: R9.2, U3.46 (USB_DM)
unnamed: R8.2, U3.47 (USB_DP)
unnamed: C12.2, U3.20 (XIN), Y1.3
unnamed: R11.2, U3.21 (XOUT)
unnamed: R13.2, R14.1, U4.3 (+)
unnamed: C22.1, R17.1, R18.2, U4.5 (+)
unnamed: C23.1, R16.1, R19.2, U4.6 (-)
unnamed: R21.2, R22.1, U5.3 (+)
unnamed: C28.1, R25.1, R26.2, U5.5 (+)
unnamed: C29.1, R24.1, R27.2, U5.6 (-)
unnamed: R29.2, R30.1, U6.3 (+)
unnamed: C34.1, R33.1, R34.2, U6.5 (+)
unnamed: C35.1, R32.1, R35.2, U6.6 (-)
unnamed: R37.2, R38.1, U7.3 (+)
unnamed: C40.1, R41.1, R42.2, U7.5 (+)
unnamed: C41.1, R40.1, R43.2, U7.6 (-)
VCC: C1.1, C18.1, C24.1, C30.1, C36.1, D17.1 (K), D18.1 (K), R13.1, R21.1, R29.1, R37.1, U1.3 (VI), U4.8 (V+), U5.8 (V+), U6.8 (V+), U7.8 (V+)

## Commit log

2023-12-28 add custom footprints
2023-12-28 add r1.0 design files
2023-12-28 add schematic and PCB overview PDF
2023-12-28 add readme and images
2023-12-28 add PDFs and production file update (no significant changes)
2023-12-28 add license statement
2024-01-09 final ordered R1.0 pcb
2024-01-09 update gitignore
2024-01-18 commit old notes in README
2024-01-18 start micropython readout
2024-01-18 add notes on R1 commissioning to README
2024-01-18 add image of R1.0 PCB
2024-01-21 start c++ firmware (starting with ADC DMA stuff)
2024-01-21 add more notes on r1.0 to README
2024-01-21 adjustments in trying to get digitization to work properly
2024-01-21 add version info during compilation
2024-01-21 create other folder to clean up the main folder
2024-01-22 first pulse recordings
2024-01-24 clean up main.cpp
2024-01-24 adjust the adc data queue to add timestamps and block indices
2024-01-24 add timestamps and overflow status to trigger waveform print
2024-01-24 implement basic user interface
2024-01-24 implement more user interface commands
2024-01-27 start implementing a python interface
2024-01-27 clean up serial interface implementation
2024-01-27 move all hardware files to one folder
2024-01-27 more moving of folders
2024-01-27 add a readme to old micropython firmware folder
2024-01-27 notes on noise levels
2024-01-27 add basic spice simulations
2024-01-27 add noise analysis script
2024-01-27 add noise measuremnt result and KCl rate
2024-01-27 fix README
2024-01-28 implement a way to record triggered waveforms with python interface
2024-01-28 commit old python interface script status before cleaning up
2024-01-28 move python interface to top level folder
2024-01-28 move source code to a seperate folder to clean up the firmware build environment
2024-01-28 add info on building and flashing
2024-01-28 adjustment to README
2024-01-28 adjust READMEs
2024-01-28 add action that builds the firmware
2024-01-28 remove unused usb library import that adds a dependency
2024-01-28 add build status badge to README
2024-01-28 Add Actions (#1)
    * add action that builds the firmware
    * remove unused usb library import that adds a dependency
    * add build status badge to README
2024-01-28 python interface: add live plotting to main and read sample rate from device
2024-01-28 firmware: implement more effecient HPF
2024-01-28 add script to record measurements
2024-01-28 implement full waveform triggers on sample block edges
2024-01-28 adjustments to python readout for new variables
2024-01-28 fix off-by one affecting waveform length in edge cases
2024-02-04 start with r2.0
2024-02-07 main r2.0 design done
2024-02-07 add r2.0 mid panel pcb
2024-02-07 add top panel pcb
2024-03-13 adjust HPF design to be closer to limit
2024-03-13 add command to switch adc channel
2024-03-13 add command to disable blinking led
2024-03-13 add command to retrieve unique flash id
2024-03-13 clean up plotting and improve buffer clearing in python scripts
2024-07-02 add r2.0 schematic
2024-07-14 Update README.md
    Fixing links and starting to represent revision 2 correctly in the readme.
2024-07-14 add picture for README
2024-07-14 Update README.md
    Center table content
2024-07-14 README: fix r2 schematic link
2024-07-14 Update README.md
    fix link
2024-07-15 hardware: add r2.0 pdf files
2024-07-15 Clean up Readme links to documents (#3)
    * README: fix r2 schematic link
    * Update README.md
    fix link
    * Update README.md
    * hardware: add r2.0 pdf files
    * Update README.md
2024-07-31 python interface: changes to spectrum plotting script
2024-07-31 python interface: Add plotting script for trigger rate scan comparison
2024-07-31 firmware: minor code cleanup
2024-07-31 hardware: add new mid panel to make the device look nicer
2024-07-31 python interface: record more information about the used board and configuration
2024-07-31 python interface: add commands (get flash ID, select ADC channel)
2024-07-31 hardware: updated kicad version
2024-07-31 minor adjustments to amplifier simulation
